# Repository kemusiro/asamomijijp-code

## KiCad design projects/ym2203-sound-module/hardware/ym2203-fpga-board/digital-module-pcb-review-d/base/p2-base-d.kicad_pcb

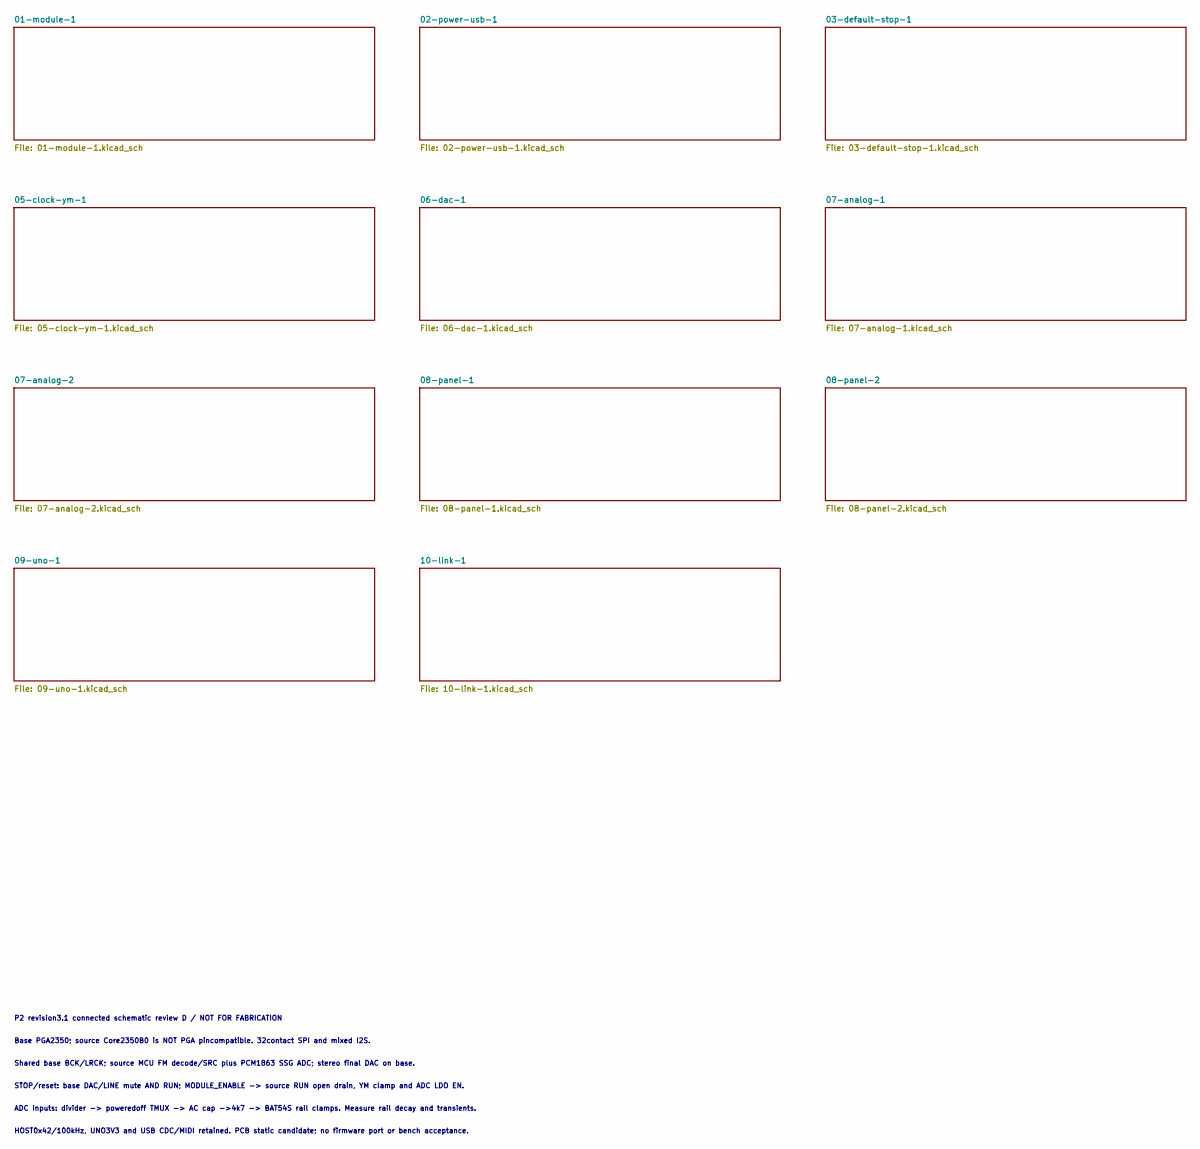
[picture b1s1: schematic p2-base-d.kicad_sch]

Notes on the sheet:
P2 revision3.1 connected schematic review D / NOT FOR FABRICATION
Base PGA2350; source Core2350B0 is NOT PGA pincompatible. 32contact SPI and mixed I2S.
Shared base BCK/LRCK; source MCU FM decode/SRC plus PCM1863 SSG ADC; stereo final DAC on base.
STOP/reset: base DAC/LINE mute AND RUN; MODULE_ENABLE -> source RUN open drain, YM clamp and ADC LDO EN.
ADC inputs: divider -> poweredoff TMUX -> AC cap ->4k7 -> BAT54S rail clamps. Measure rail decay and transients.
HOST0x42/100kHz, UNO3V3 and USB CDC/MIDI retained. PCB static candidate; no firmware port or bench acceptance.

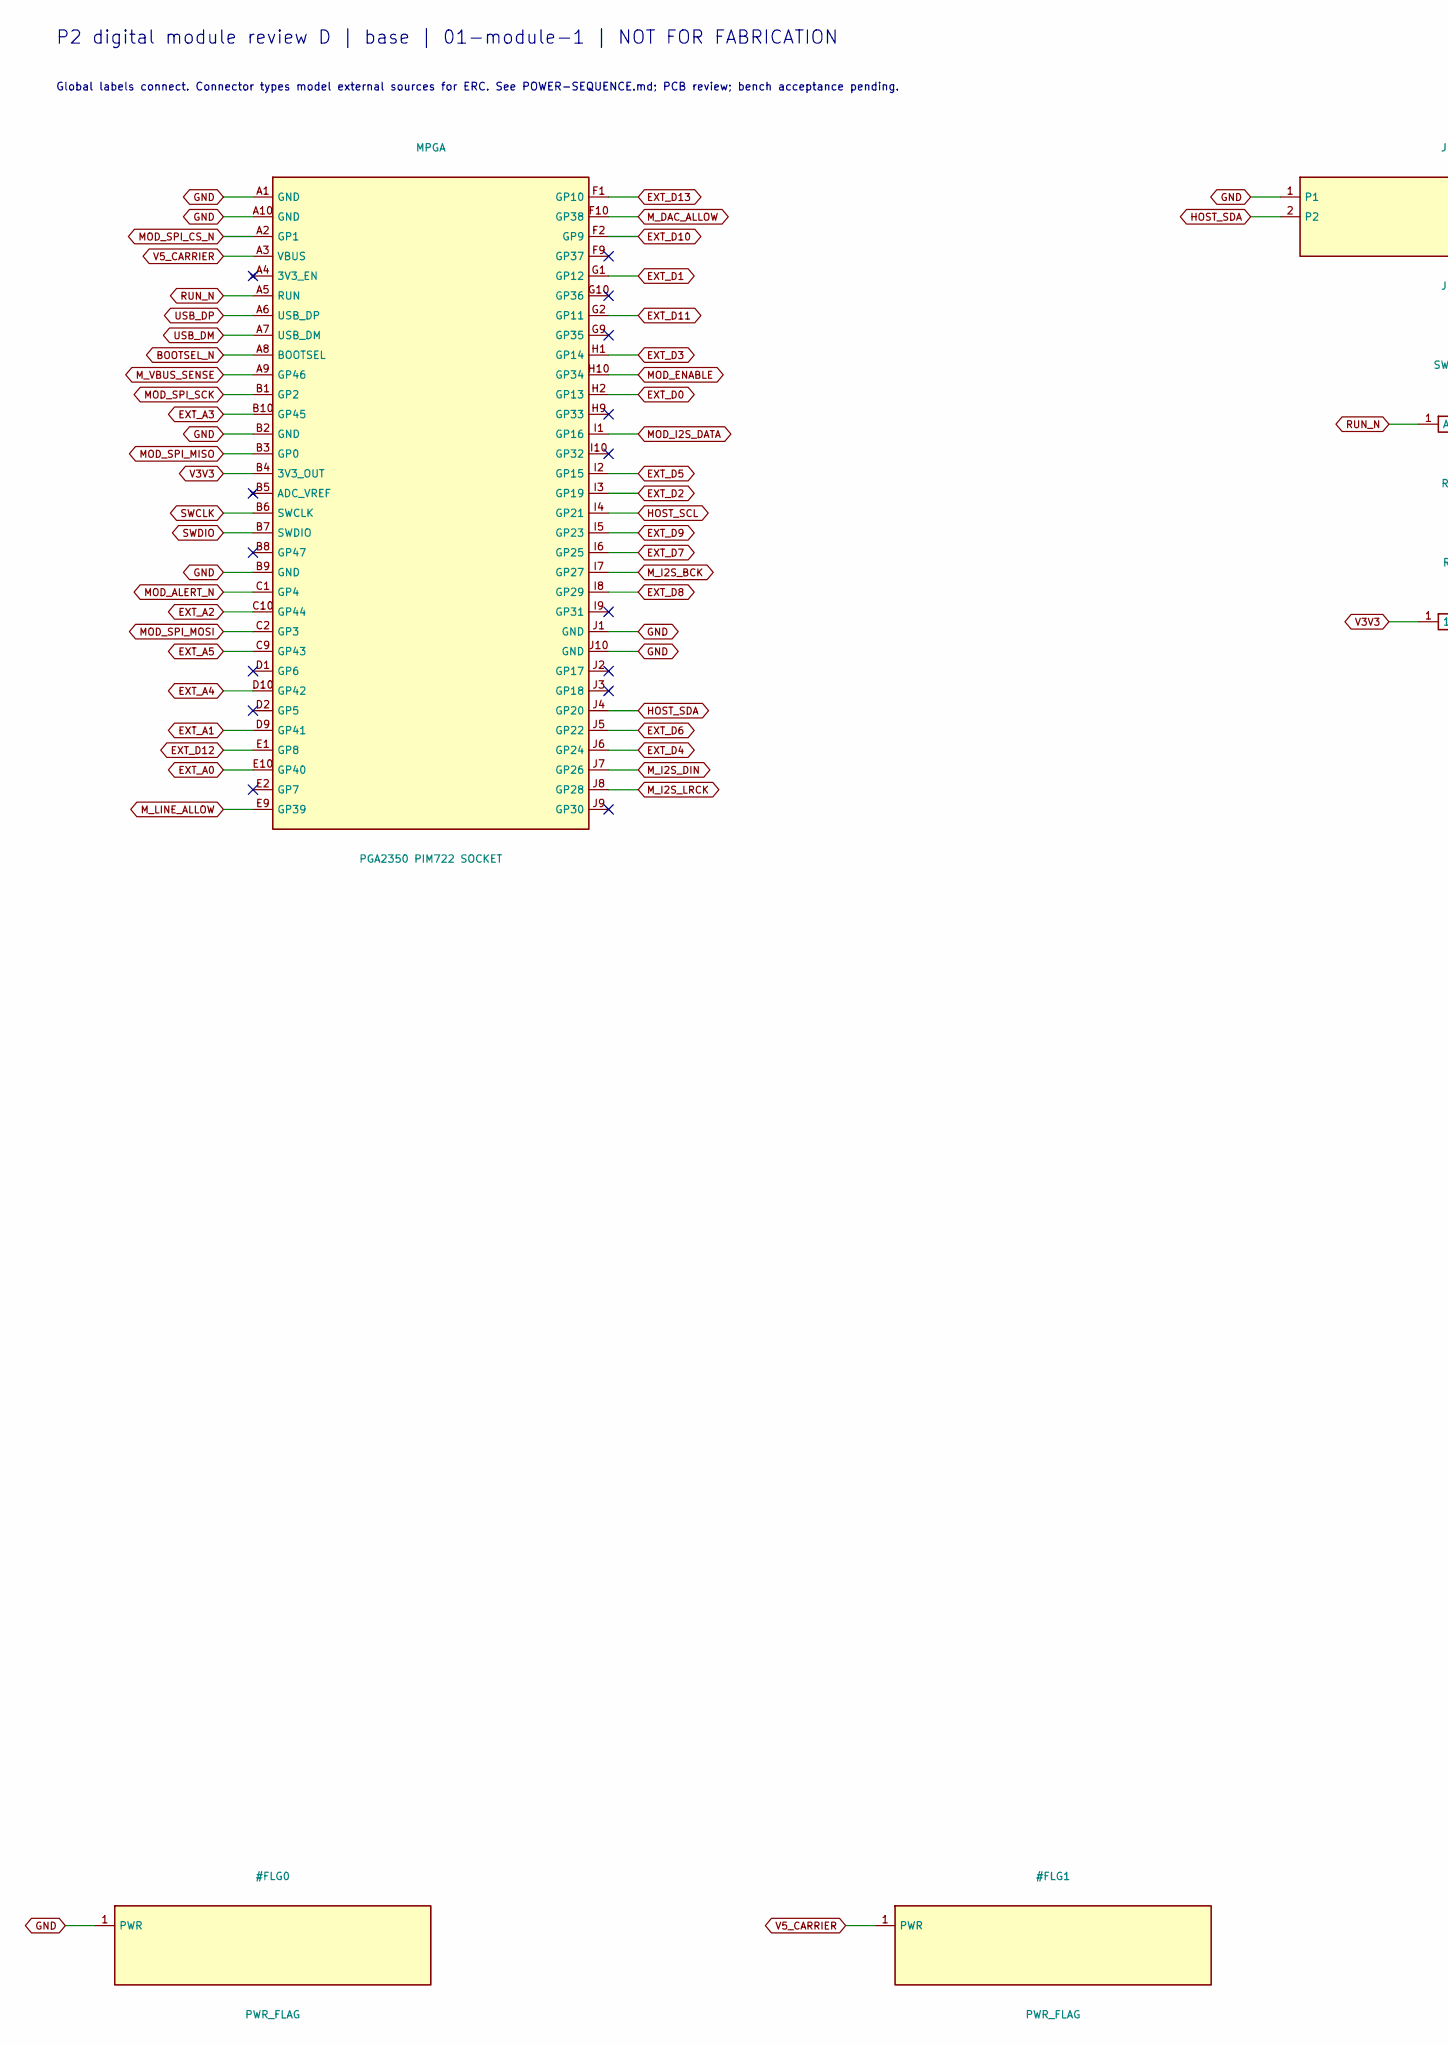
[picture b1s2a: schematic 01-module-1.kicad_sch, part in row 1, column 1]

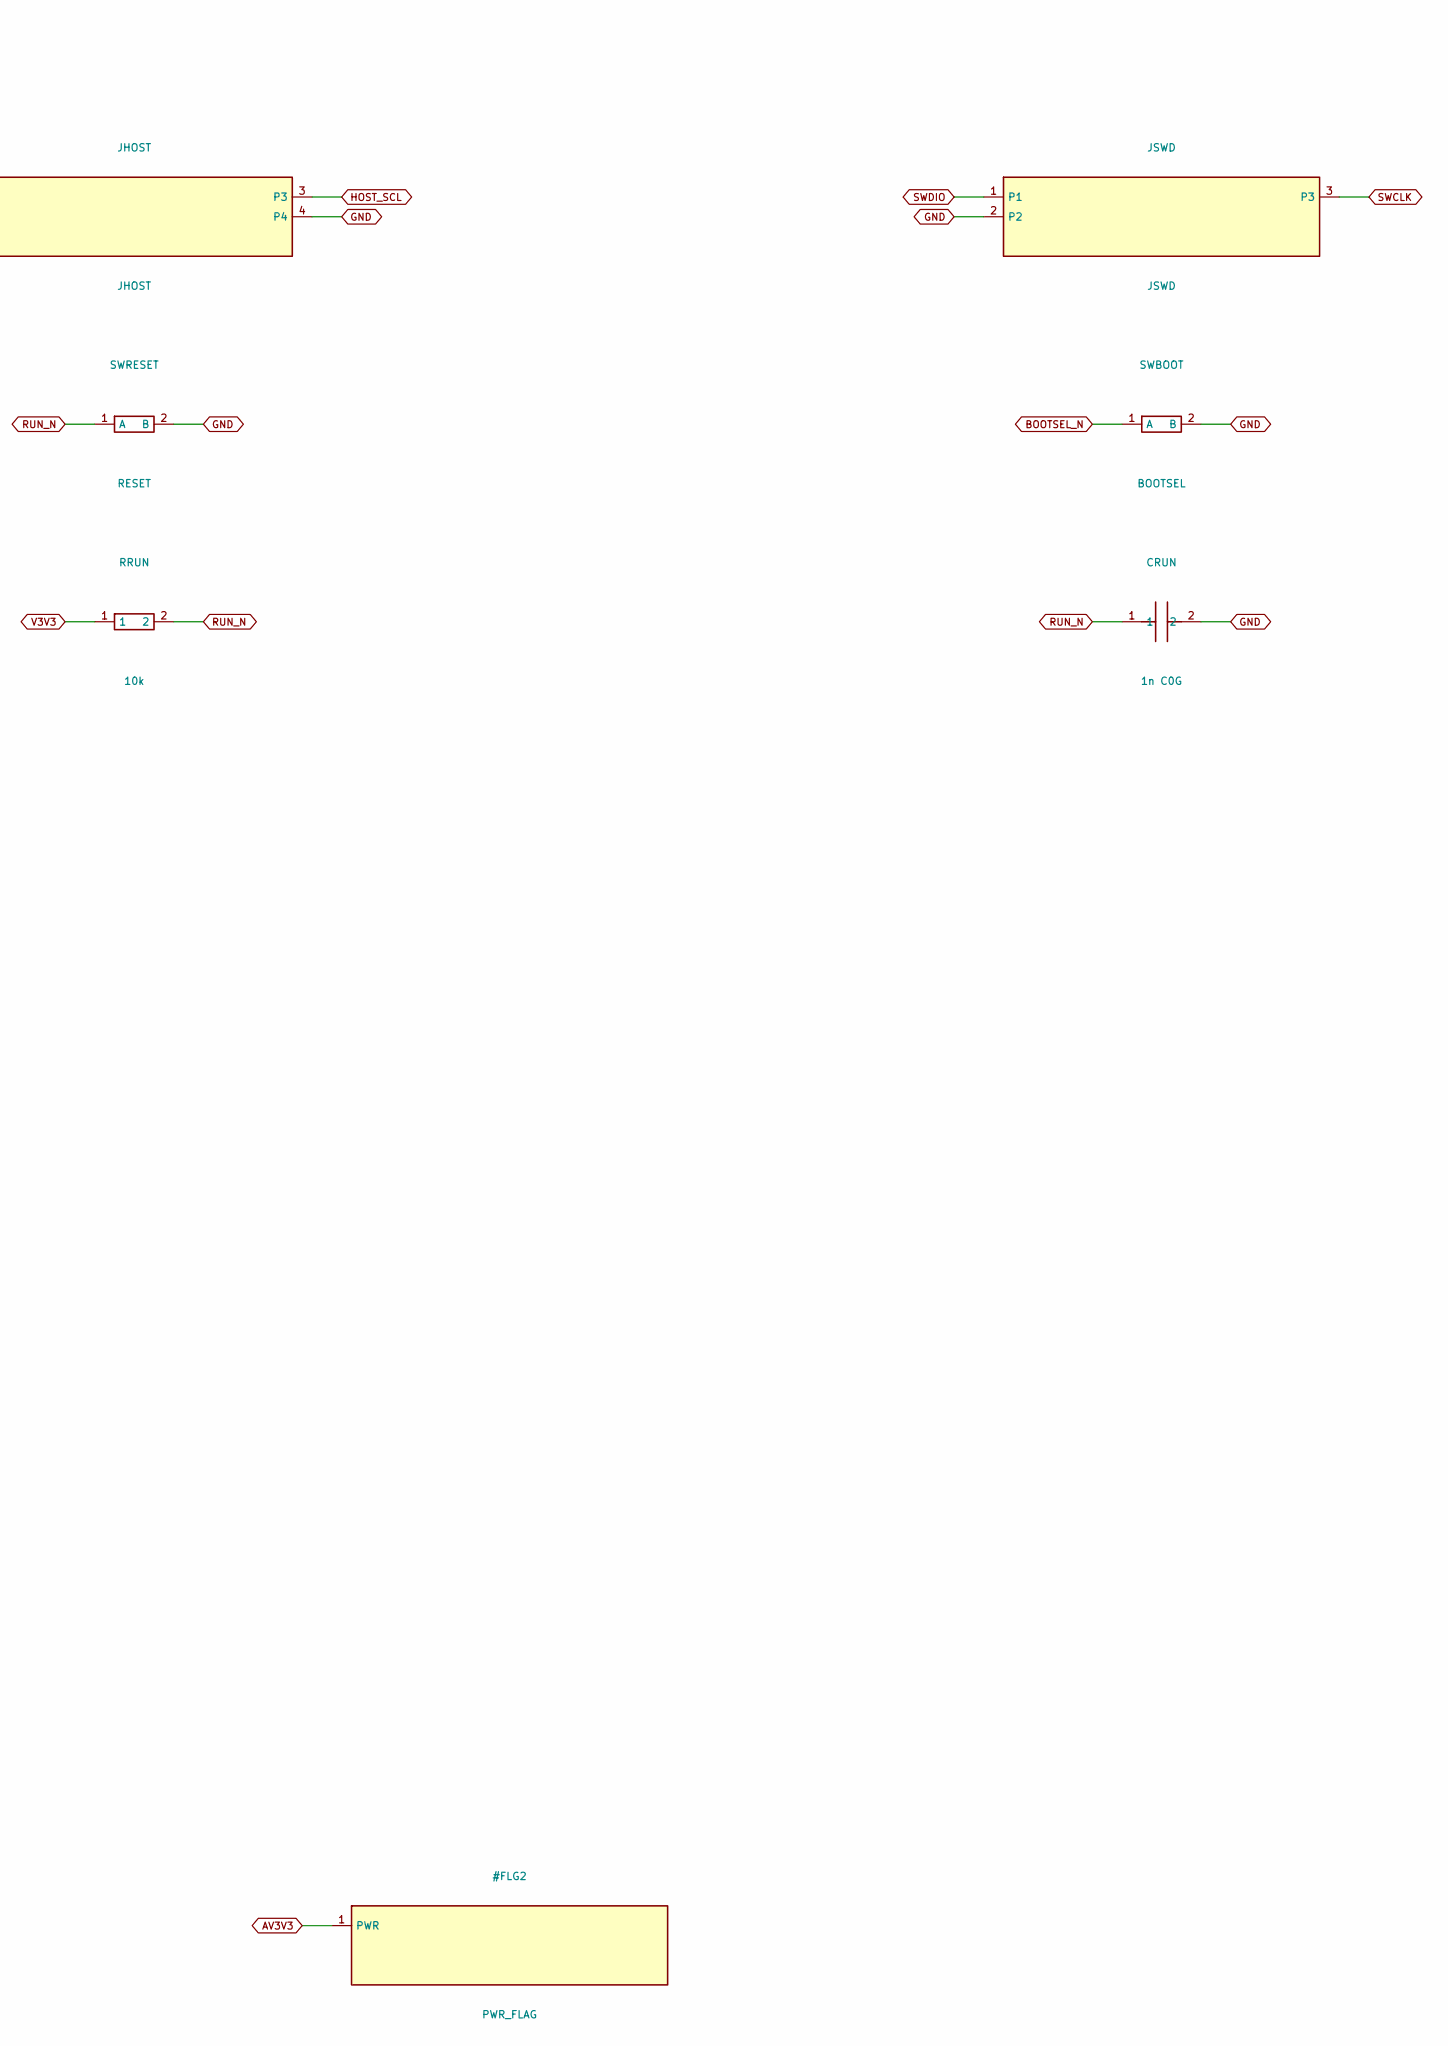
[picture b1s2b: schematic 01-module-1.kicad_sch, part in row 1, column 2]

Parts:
CRUN: 1n C0G; C_0805_2012Metric
JHOST: JHOST; PinHeader_1x04_P2.54mm_Vertical
JSWD: JSWD; PinHeader_1x03_P2.54mm_Vertical
MPGA: PGA2350 PIM722 SOCKET; PGA2350_Socket_64
RRUN: 10k; R_0805_2012Metric
SWBOOT: BOOTSEL; SW_PUSH_6mm_H4.3mm
SWRESET: RESET; SW_PUSH_6mm_H4.3mm

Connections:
BOOTSEL_N: MPGA.A8 (BOOTSEL), SWBOOT.1 (A)
EXT_A0: MPGA.E10 (GP40); also elsewhere on the board
EXT_A1: MPGA.D9 (GP41); also elsewhere on the board
EXT_A2: MPGA.C10 (GP44); also elsewhere on the board
EXT_A3: MPGA.B10 (GP45); also elsewhere on the board
EXT_A4: MPGA.D10 (GP42); also elsewhere on the board
EXT_A5: MPGA.C9 (GP43); also elsewhere on the board
EXT_D0: MPGA.H2 (GP13); also elsewhere on the board
EXT_D1: MPGA.G1 (GP12); also elsewhere on the board
EXT_D2: MPGA.I3 (GP19); also elsewhere on the board
EXT_D3: MPGA.H1 (GP14); also elsewhere on the board
EXT_D4: MPGA.J6 (GP24); also elsewhere on the board
EXT_D5: MPGA.I2 (GP15); also elsewhere on the board
EXT_D6: MPGA.J5 (GP22); also elsewhere on the board
EXT_D7: MPGA.I6 (GP25); also elsewhere on the board
EXT_D8: MPGA.I8 (GP29); also elsewhere on the board
EXT_D9: MPGA.I5 (GP23); also elsewhere on the board
EXT_D10: MPGA.F2 (GP9); also elsewhere on the board
EXT_D11: MPGA.G2 (GP11); also elsewhere on the board
EXT_D12: MPGA.E1 (GP8); also elsewhere on the board
EXT_D13: MPGA.F1 (GP10); also elsewhere on the board
GND: CRUN.2, JHOST.1, JHOST.4, JSWD.2, MPGA.A1 (GND), MPGA.A10 (GND), MPGA.B2 (GND), MPGA.B9 (GND), MPGA.J1 (GND), MPGA.J10 (GND), SWBOOT.2 (B), SWRESET.2 (B); also elsewhere on the board
HOST_SCL: JHOST.3, MPGA.I4 (GP21); also elsewhere on the board
HOST_SDA: JHOST.2, MPGA.J4 (GP20); also elsewhere on the board
MOD_ALERT_N: MPGA.C1 (GP4); also elsewhere on the board
MOD_ENABLE: MPGA.H10 (GP34); also elsewhere on the board
MOD_I2S_DATA: MPGA.I1 (GP16); also elsewhere on the board
MOD_SPI_CS_N: MPGA.A2 (GP1); also elsewhere on the board
MOD_SPI_MISO: MPGA.B3 (GP0); also elsewhere on the board
MOD_SPI_MOSI: MPGA.C2 (GP3); also elsewhere on the board
MOD_SPI_SCK: MPGA.B1 (GP2); also elsewhere on the board
M_DAC_ALLOW: MPGA.F10 (GP38); also elsewhere on the board
M_I2S_BCK: MPGA.I7 (GP27); also elsewhere on the board
M_I2S_DIN: MPGA.J7 (GP26); also elsewhere on the board
M_I2S_LRCK: MPGA.J8 (GP28); also elsewhere on the board
M_LINE_ALLOW: MPGA.E9 (GP39); also elsewhere on the board
M_VBUS_SENSE: MPGA.A9 (GP46); also elsewhere on the board
RUN_N: CRUN.1, MPGA.A5 (RUN), RRUN.2, SWRESET.1 (A); also elsewhere on the board
SWCLK: JSWD.3, MPGA.B6 (SWCLK)
SWDIO: JSWD.1, MPGA.B7 (SWDIO)
USB_DM: MPGA.A7 (USB_DM); also elsewhere on the board
USB_DP: MPGA.A6 (USB_DP); also elsewhere on the board
V3V3: MPGA.B4 (3V3_OUT), RRUN.1; also elsewhere on the board
V5_CARRIER: MPGA.A3 (VBUS); also elsewhere on the board

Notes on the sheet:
P2 digital module review D | base | 01-module-1 | NOT FOR FABRICATION
Global labels connect. Connector types model external sources for ERC. See POWER-SEQUENCE.md; PCB review; bench acceptance pending.

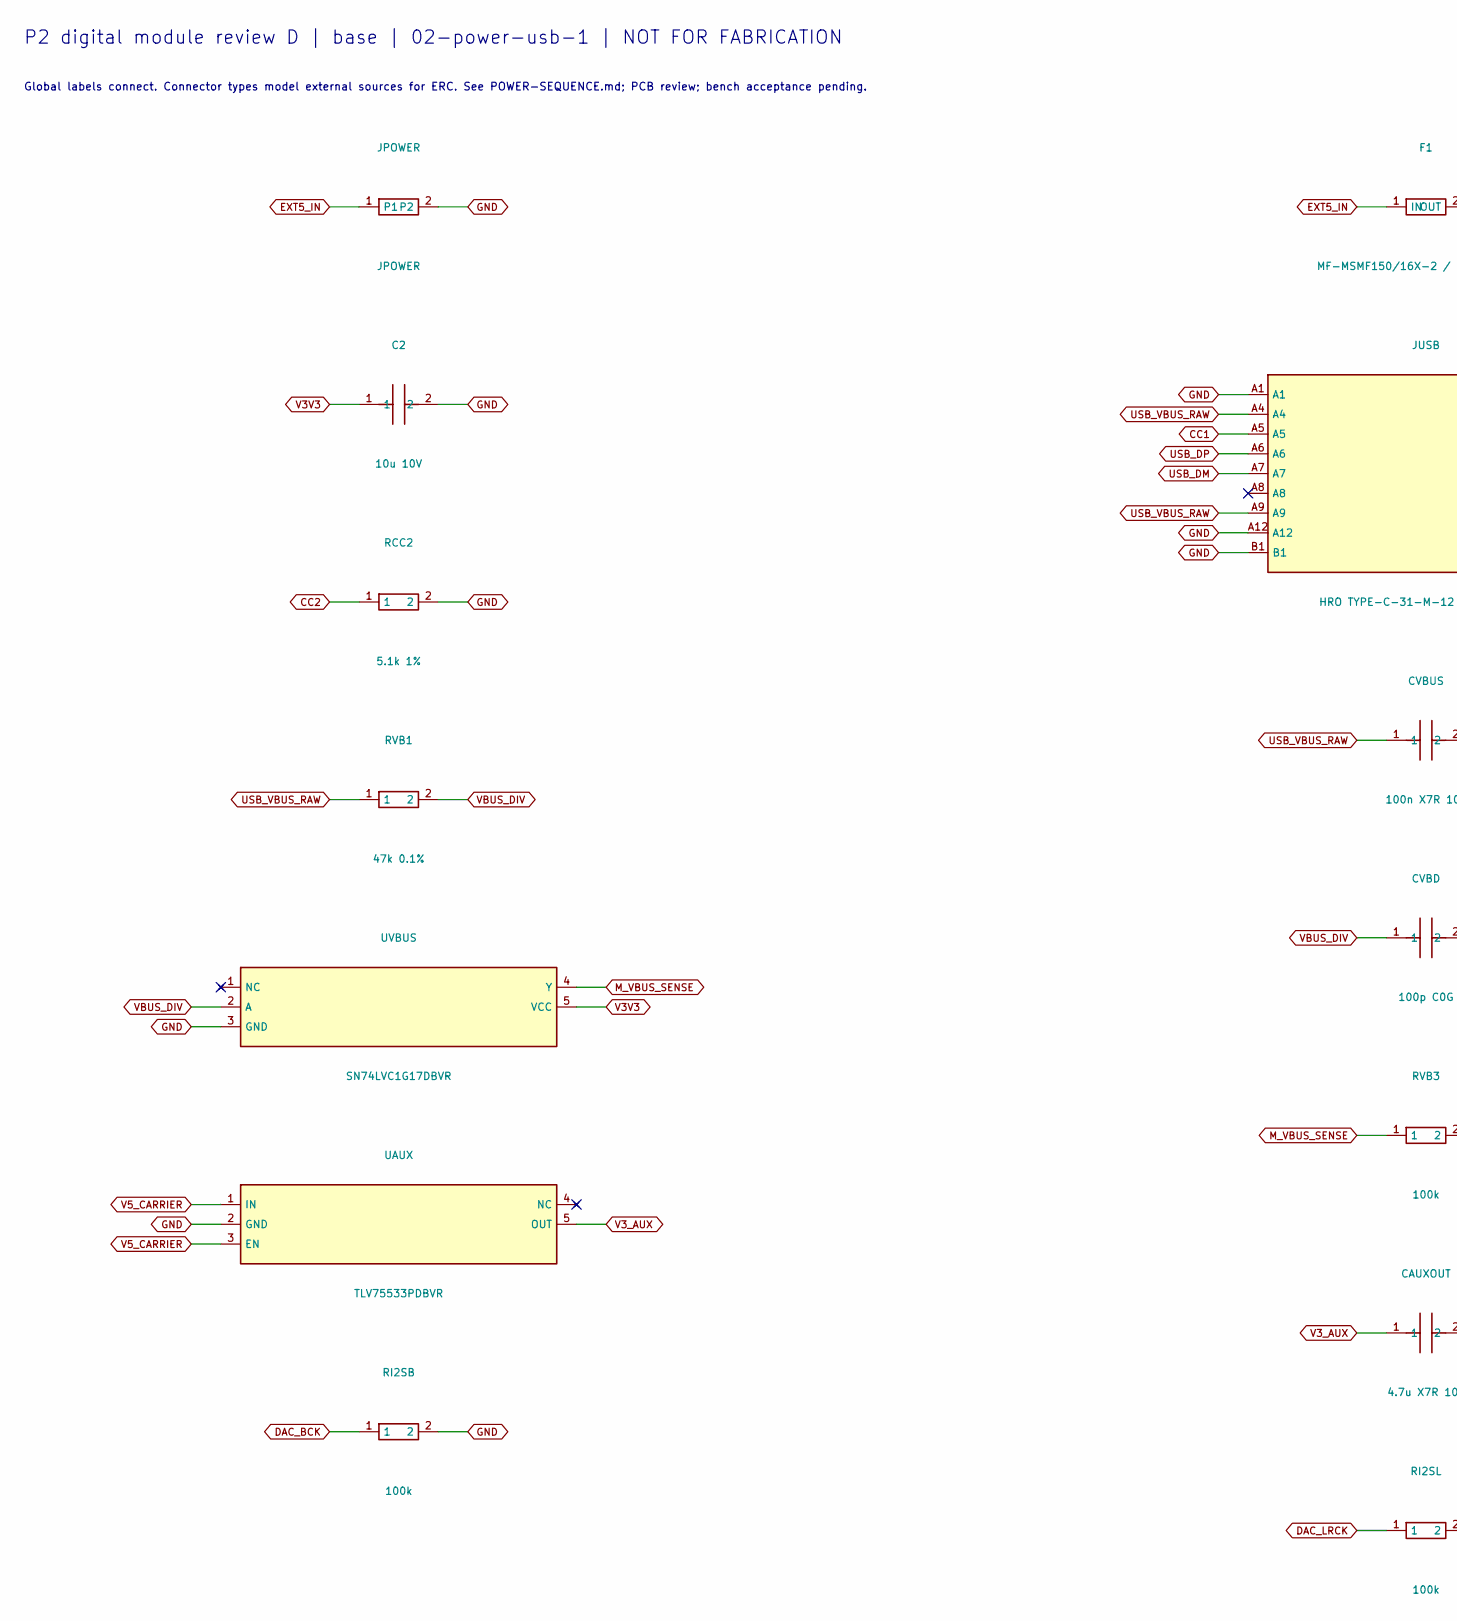
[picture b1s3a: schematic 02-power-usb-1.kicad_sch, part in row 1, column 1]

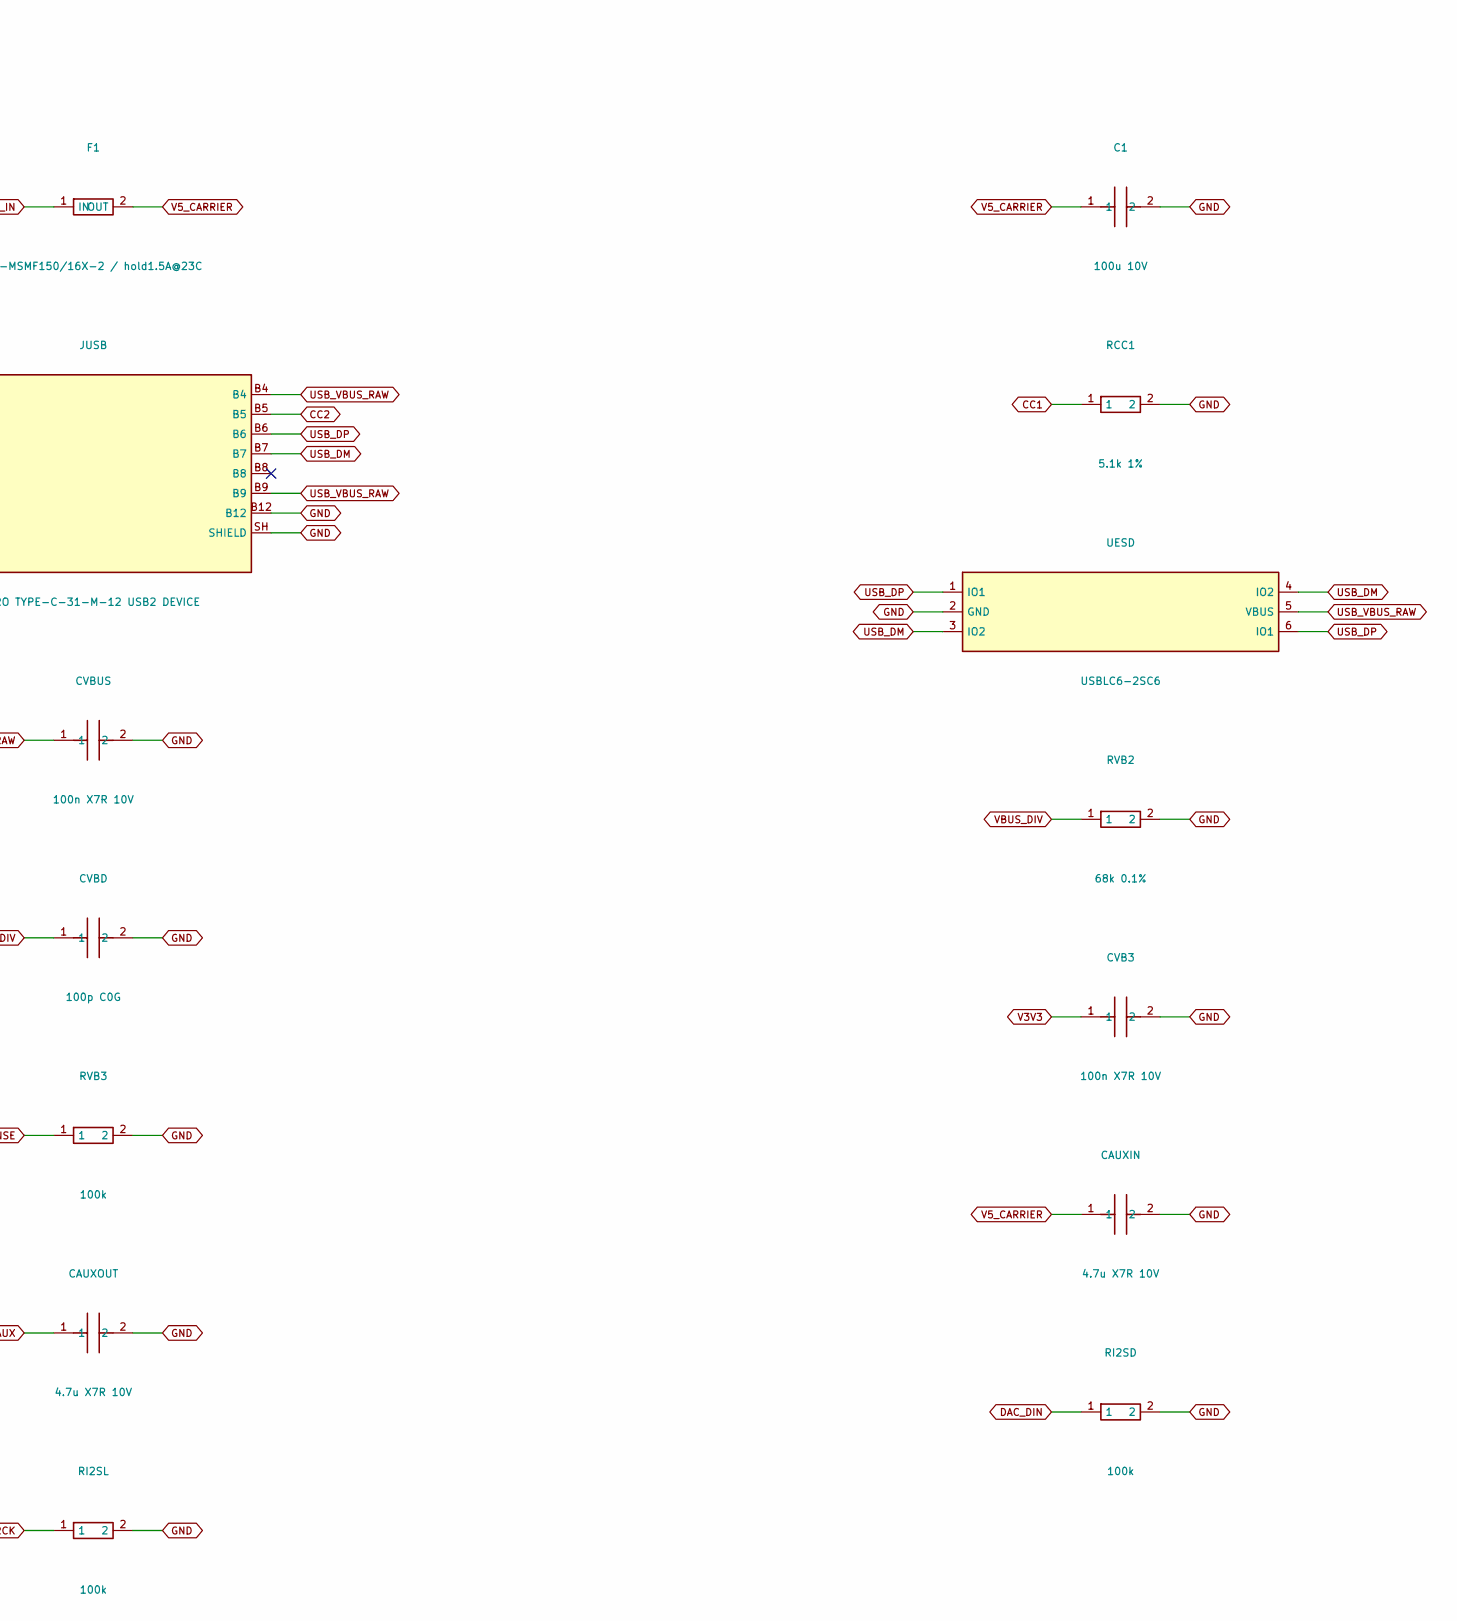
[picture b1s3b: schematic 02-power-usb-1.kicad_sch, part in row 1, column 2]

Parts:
C1: 100u 10V; CP_Radial_D6.3mm_P2.50mm
C2: 10u 10V; C_0805_2012Metric
CAUXIN: 4.7u X7R 10V; C_0805_2012Metric
CAUXOUT: 4.7u X7R 10V; C_0805_2012Metric
CVB3: 100n X7R 10V; C_0805_2012Metric
CVBD: 100p C0G; C_0805_2012Metric
CVBUS: 100n X7R 10V; C_0805_2012Metric
F1: MF-MSMF150/16X-2 / hold1.5A@23C; Fuse_1812_4532Metric
JPOWER: JPOWER; PinHeader_1x02_P2.54mm_Vertical
JUSB: HRO TYPE-C-31-M-12 USB2 DEVICE; USB_C_Receptacle_HRO_TYPE-C-31-M-12
RCC1, RCC2: 5.1k 1%; R_0805_2012Metric
RI2SB, RI2SD, RI2SL: 100k; R_0805_2012Metric
RVB1: 47k 0.1%; R_0805_2012Metric
RVB2: 68k 0.1%; R_0805_2012Metric
RVB3: 100k; R_0805_2012Metric
UAUX: TLV75533PDBVR; SOT-23-5
UESD: USBLC6-2SC6; SOT-23-6
UVBUS: SN74LVC1G17DBVR; SOT-23-5

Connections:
CC1: JUSB.A5, RCC1.1
CC2: JUSB.B5, RCC2.1
DAC_BCK: RI2SB.1; also elsewhere on the board
DAC_DIN: RI2SD.1; also elsewhere on the board
DAC_LRCK: RI2SL.1; also elsewhere on the board
EXT5_IN: F1.1 (IN), JPOWER.1
GND: C1.2, C2.2, CAUXIN.2, CAUXOUT.2, CVB3.2, CVBD.2, CVBUS.2, JPOWER.2, JUSB.A1, JUSB.A12, JUSB.B1, JUSB.B12, JUSB.SH (SHIELD), RCC1.2, RCC2.2, RI2SB.2, RI2SD.2, RI2SL.2, RVB2.2, RVB3.2, UAUX.2 (GND), UESD.2 (GND), UVBUS.3 (GND); also elsewhere on the board
M_VBUS_SENSE: RVB3.1, UVBUS.4 (Y); also elsewhere on the board
USB_DM: JUSB.A7, JUSB.B7, UESD.3 (IO2), UESD.4 (IO2); also elsewhere on the board
USB_DP: JUSB.A6, JUSB.B6, UESD.1 (IO1), UESD.6 (IO1); also elsewhere on the board
USB_VBUS_RAW: CVBUS.1, JUSB.A4, JUSB.A9, JUSB.B4, JUSB.B9, RVB1.1, UESD.5 (VBUS)
V3V3: C2.1, CVB3.1, UVBUS.5 (VCC); also elsewhere on the board
V3_AUX: CAUXOUT.1, UAUX.5 (OUT); also elsewhere on the board
V5_CARRIER: C1.1, CAUXIN.1, F1.2 (OUT), UAUX.1 (IN), UAUX.3 (EN); also elsewhere on the board
VBUS_DIV: CVBD.1, RVB1.2, RVB2.1, UVBUS.2 (A)

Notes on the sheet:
P2 digital module review D | base | 02-power-usb-1 | NOT FOR FABRICATION
Global labels connect. Connector types model external sources for ERC. See POWER-SEQUENCE.md; PCB review; bench acceptance pending.

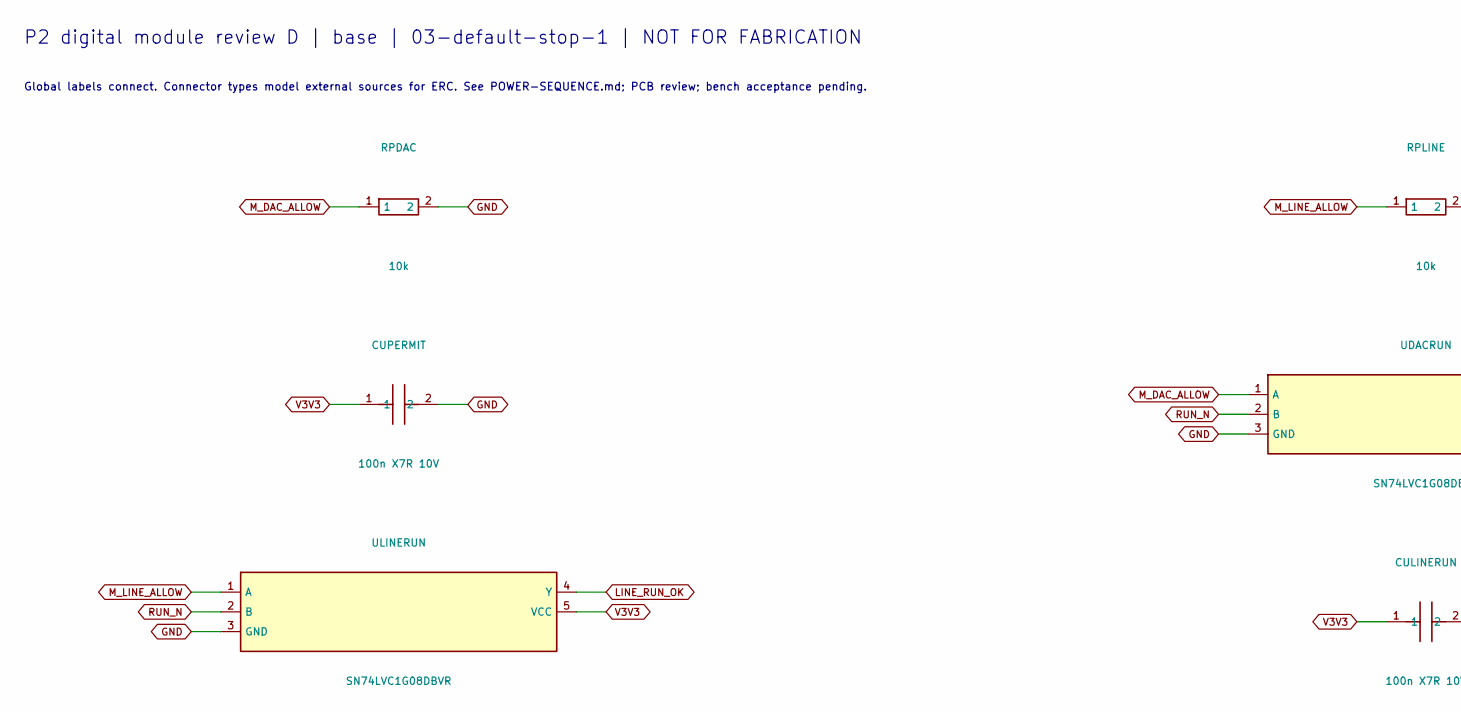
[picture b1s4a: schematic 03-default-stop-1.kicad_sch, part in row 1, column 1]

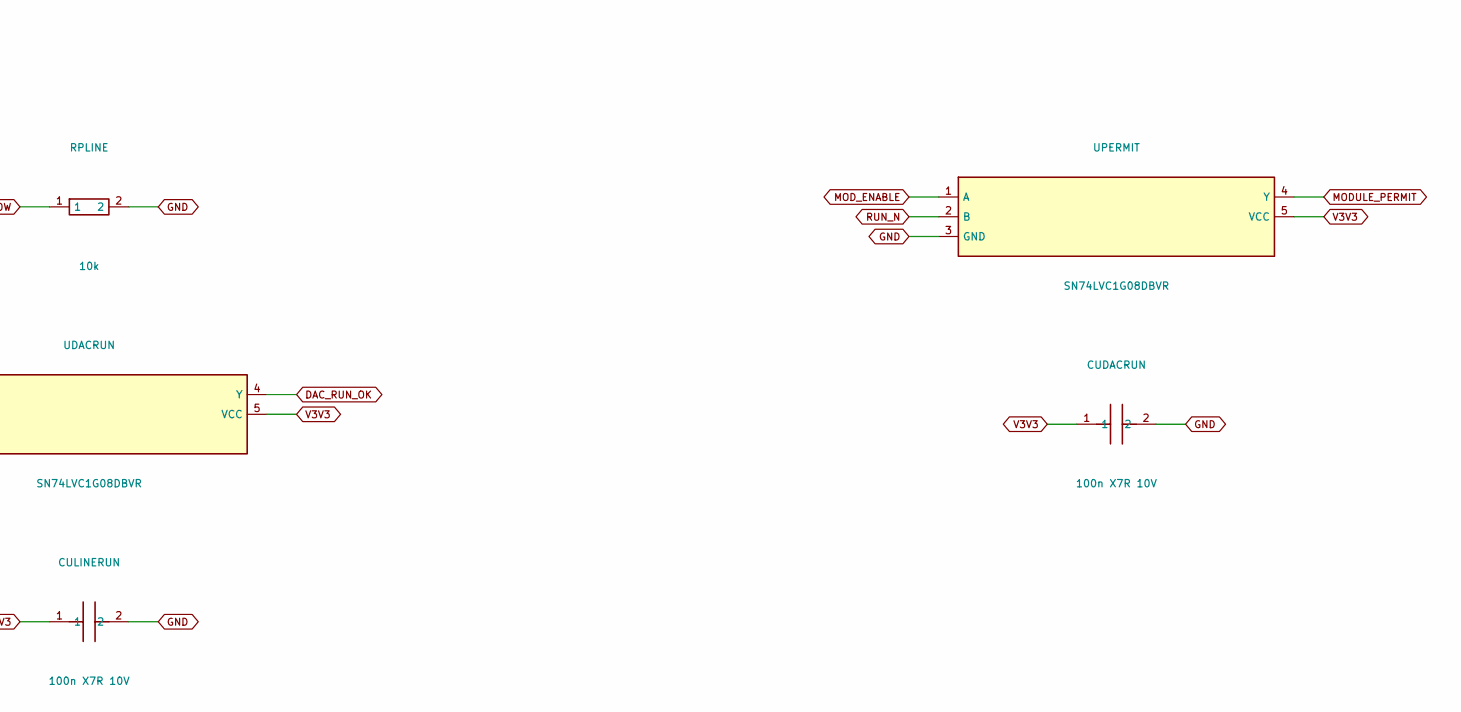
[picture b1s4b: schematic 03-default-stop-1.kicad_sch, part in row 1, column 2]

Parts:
CUDACRUN: 100n X7R 10V; C_0805_2012Metric
CULINERUN: 100n X7R 10V; C_0805_2012Metric
CUPERMIT: 100n X7R 10V; C_0805_2012Metric
RPDAC: 10k; R_0805_2012Metric
RPLINE: 10k; R_0805_2012Metric
UDACRUN: SN74LVC1G08DBVR; SOT-23-5
ULINERUN: SN74LVC1G08DBVR; SOT-23-5
UPERMIT: SN74LVC1G08DBVR; SOT-23-5

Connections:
DAC_RUN_OK: UDACRUN.4 (Y); also elsewhere on the board
GND: CUDACRUN.2, CULINERUN.2, CUPERMIT.2, RPDAC.2, RPLINE.2, UDACRUN.3 (GND), ULINERUN.3 (GND), UPERMIT.3 (GND); also elsewhere on the board
LINE_RUN_OK: ULINERUN.4 (Y); also elsewhere on the board
MODULE_PERMIT: UPERMIT.4 (Y); also elsewhere on the board
MOD_ENABLE: UPERMIT.1 (A); also elsewhere on the board
M_DAC_ALLOW: RPDAC.1, UDACRUN.1 (A); also elsewhere on the board
M_LINE_ALLOW: RPLINE.1, ULINERUN.1 (A); also elsewhere on the board
RUN_N: UDACRUN.2 (B), ULINERUN.2 (B), UPERMIT.2 (B); also elsewhere on the board
V3V3: CUDACRUN.1, CULINERUN.1, CUPERMIT.1, UDACRUN.5 (VCC), ULINERUN.5 (VCC), UPERMIT.5 (VCC); also elsewhere on the board

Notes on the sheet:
P2 digital module review D | base | 03-default-stop-1 | NOT FOR FABRICATION
Global labels connect. Connector types model external sources for ERC. See POWER-SEQUENCE.md; PCB review; bench acceptance pending.

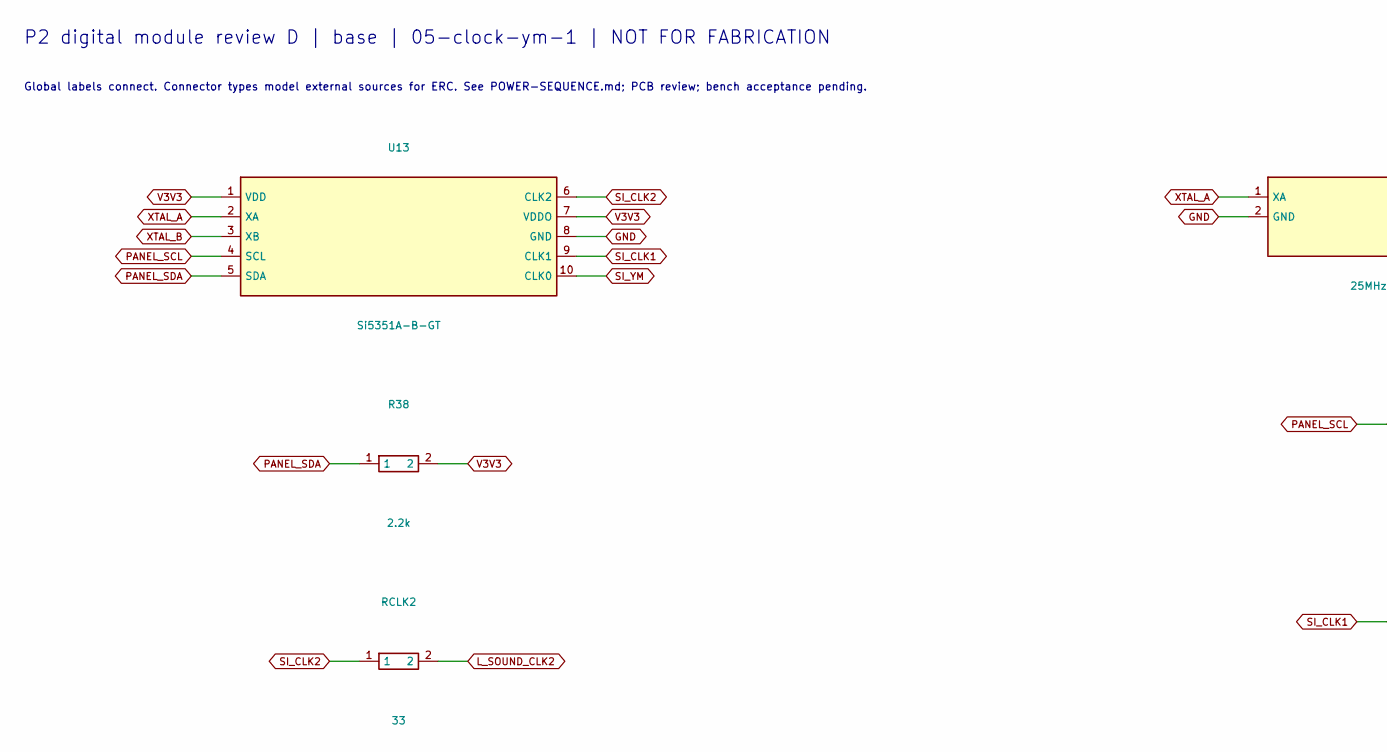
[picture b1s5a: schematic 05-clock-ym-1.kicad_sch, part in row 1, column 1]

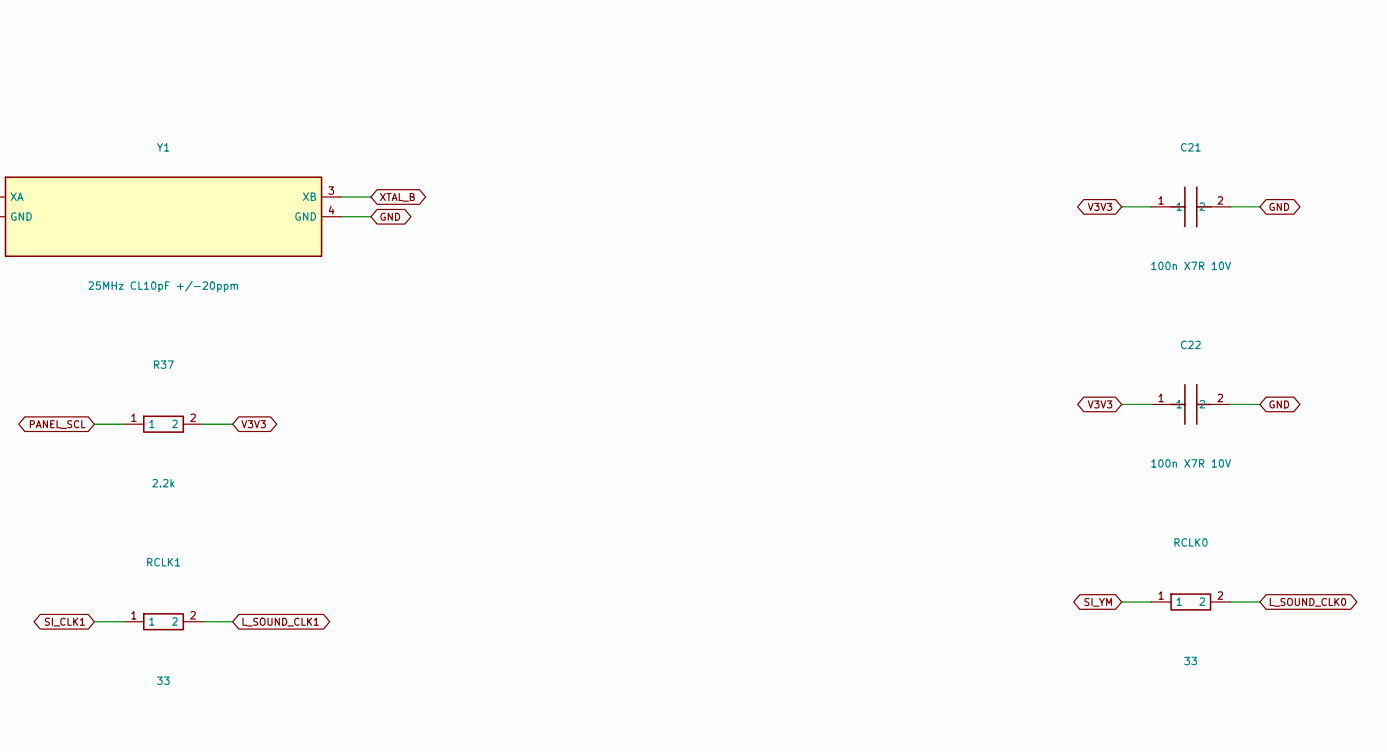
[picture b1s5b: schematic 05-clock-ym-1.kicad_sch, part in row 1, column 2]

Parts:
C21, C22: 100n X7R 10V; C_0805_2012Metric
R37, R38: 2.2k; R_0805_2012Metric
RCLK0, RCLK1, RCLK2: 33; R_0805_2012Metric
U13: Si5351A-B-GT; MSOP-10_3x3mm_P0.5mm
Y1: 25MHz CL10pF +/-20ppm; Crystal_SMD_3225-4Pin_3.2x2.5mm

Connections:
GND: C21.2, C22.2, U13.8 (GND), Y1.2 (GND), Y1.4 (GND); also elsewhere on the board
L_SOUND_CLK0: RCLK0.2; also elsewhere on the board
L_SOUND_CLK1: RCLK1.2; also elsewhere on the board
L_SOUND_CLK2: RCLK2.2; also elsewhere on the board
PANEL_SCL: R37.1, U13.4 (SCL); also elsewhere on the board
PANEL_SDA: R38.1, U13.5 (SDA); also elsewhere on the board
SI_CLK1: RCLK1.1, U13.9 (CLK1)
SI_CLK2: RCLK2.1, U13.6 (CLK2)
SI_YM: RCLK0.1, U13.10 (CLK0)
V3V3: C21.1, C22.1, R37.2, R38.2, U13.1 (VDD), U13.7 (VDDO); also elsewhere on the board
XTAL_A: U13.2 (XA), Y1.1 (XA)
XTAL_B: U13.3 (XB), Y1.3 (XB)

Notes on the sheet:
P2 digital module review D | base | 05-clock-ym-1 | NOT FOR FABRICATION
Global labels connect. Connector types model external sources for ERC. See POWER-SEQUENCE.md; PCB review; bench acceptance pending.
